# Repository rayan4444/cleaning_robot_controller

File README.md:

# Deck cleaning and staining robot

Hardware files for all the custom electronics in a deck cleaning and staining robot.
* Eagle files and documentation provided. See individual folder readme for details.
* Firmware for the STM32F407 was developed in C based on STM CubeMx libraries, but cannot be made public as of now.  

## Architecture

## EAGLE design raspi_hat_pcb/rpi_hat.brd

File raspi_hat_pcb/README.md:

# Raspberry Pi Hat

## Description
This board plugs onto a Raspberry pi and features:
- 1x ATSAMD21G18 MCU (Arduino Zero)
- 1x BNO055 IMU with jumpers to select the I2C host: Raspberry Pi or MCU
- 1x RS-485 transciever with jumper to select the UART host: Raspberry Pi or MCU
- 4x connectors for Ultrasonic sensors
- 1x FET driver for a small 5V fan to cool down the RPi

## Programming
The MCU on this board can normally be programmed directly via it's native USB port (using the microUSB connector on the board and in the Arduino IDE, choose Arduino Zero native USB as your Board. You might have to double-press the reset button before flashing). However the first time you use it, you need to burn the Arduino Zero bootloader on it first, using the SWD pins.

In this board, the SWD pins are connected to the Raspberry Pi connector so you can use the Raspberry pi to burn the bootloader, like explained in [this tutorial](https://learn.adafruit.com/programming-microcontrollers-using-openocd-on-raspberry-pi).

The soldered boards sent already have the Arduino bootloader burned and can be programmed directly.

## Hardware connections

MCU:

|ATSAMD21G18 Pin|Arduino Pin|Signal| Notes|
|:---:|:---:|:---:|:---:|
|PA5| A4 or 18|FAN_MCU| to toggle cooling fan from the MCU|
|PA10|1 or TX|MCU_TXD||
|PA11|0 or RX|MCU_RXD||
|PA12|22|RS485_DIR| controlling RS485 transceiver direction|
|PA15|5~|TRIG_B_| trigger pin for one pair of ultrasonic sensors|
|PA16| 11~|TRIG_|trigger pin for the other pair of ultrasonic sensors|
|PA17|13~|ECHO1| interrupt enabled|
|PA18|10~|ECHO2| interrupt enabled|
|PA19|12~|ECHO3|interrupt enabled|
|PA20|6~|ECHO4| interrupt enabled|
|PA21|7|IMU_INT| interrupt enabled|
|PA22|SDA|MCU_SDA| to IMU|
|PA23|SCL|MCU_SCL| to IMU|
|PA24|USB D-|USBD_N| to micro USB connector, for programming|
|PA25|USB D+|USBD_P| to micro USB connector, for programming|
|PA30|SWCLK|SWCLK|To Rpi,  for first time bootloader burning|
|PA31|SWDIO|SWDIO|To Rpi,  for first time bootlader burning|

Raspberry Pi:

|Raspberry Pi GPIO|Raspberry Pi Pin|Signal|Notes|
|:---:|:---:|:---:|:---:|
|GPIO 2|3|RPI_SDA|to IMU|
|GPIO 3|5|RPI_SCL|to IMU|
|GPIO 4|7|FAN_PI| to toggle cooling fan from the Rpi|
|GPIO 14|8|RPI_TX|RPI UART|
|GPIO 15|10|RPI_RX|RPI UART|
|GPIO 17|11|IMU_RST|to IMU|
|GPIO 18|12|RESET||
|GPIO 27|13|IMU_INT| to IMU|
|GPIO 24|18|MCU SWDIO|To burn bootloader to the MCU|
|GPIO 25|22|MCU SWCLK|To burn bootloader to the MCU|

Connectors:
- see pictures above

Jumper options:
- JP1 and JP2: select whether the MCU's UART talks to the Main board through RS485 or directly to the RPI
- JP3 and JP4: select whether the IMU connects to the MCU or the RPi

## Errata
Errors noticed when assemling:
- Pin 1 of IMU hard to spot
- Diode direction missing on D1
- R7 and C8 silkscreen unclear
- Ultrasonic sensors and RS485 connectors don't have a labelled pinout

Testing log:
- Tested all boards, bootloader burned.
- Communication with the IMU was tested with the Arduino MCU (I2C address 0x28): the jumpers were then set to commnuicate with the Raspberry Pi, but that communication hasn't been tested.
- Board 1: no problems
- Board 2: 5V red LED doesn't turn on but board works fine
- Board 3: no problems

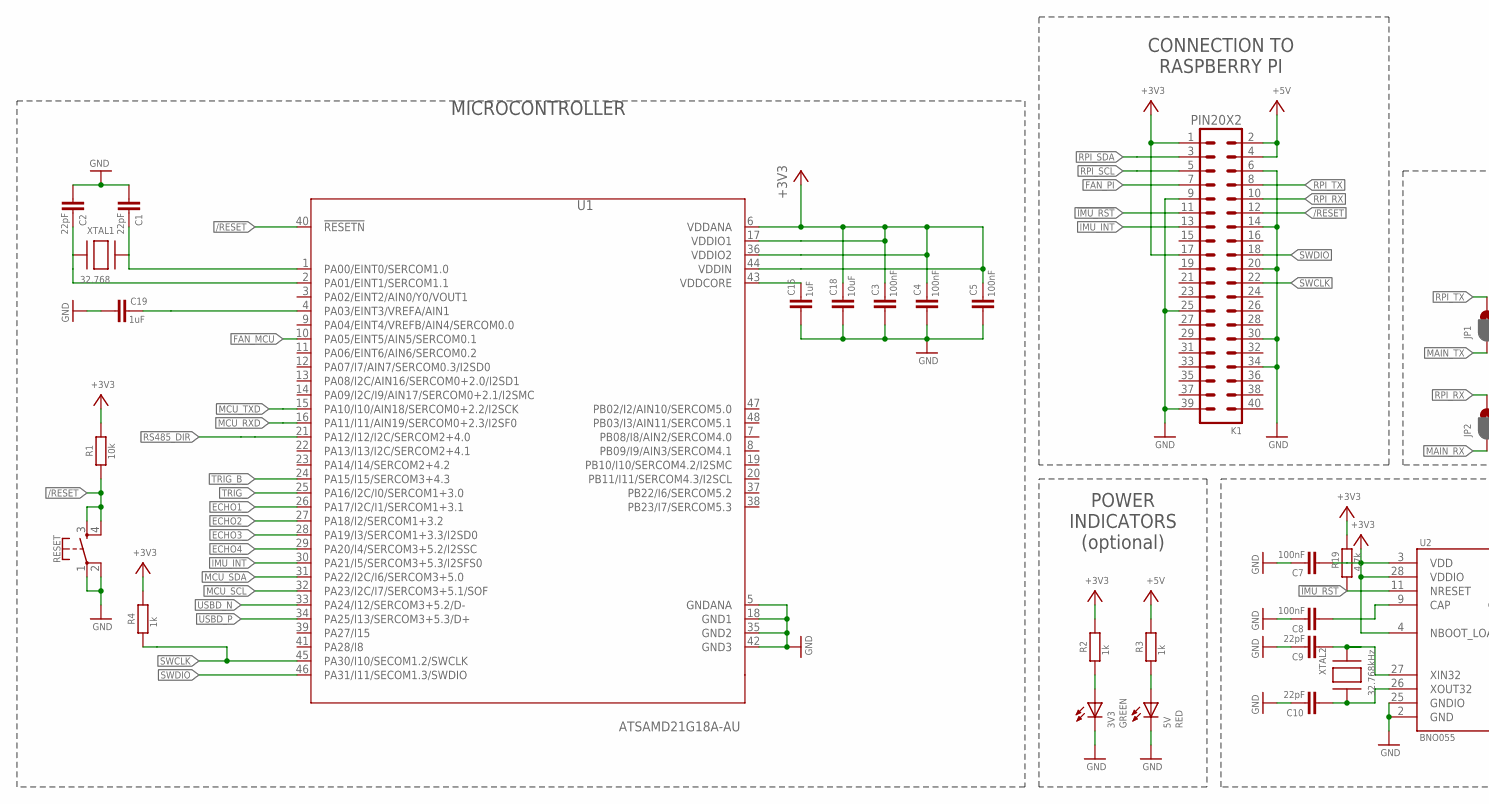
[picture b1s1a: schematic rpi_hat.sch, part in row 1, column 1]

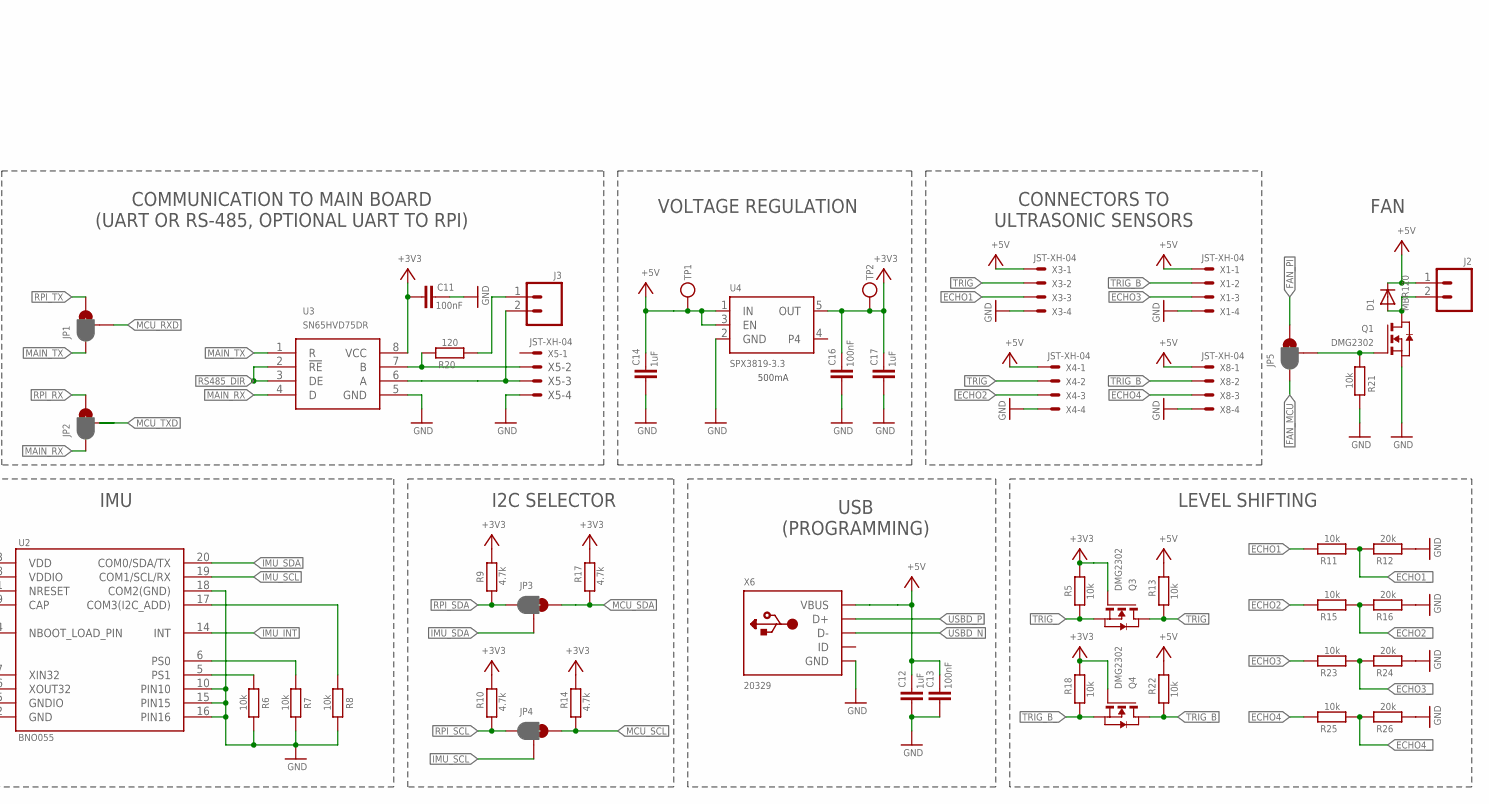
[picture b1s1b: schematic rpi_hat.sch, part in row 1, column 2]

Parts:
3V3: GREEN; CHIP-LED0603
5V: RED; CHIP-LED0603
C1, C2, C9, C10: 22pF; C0402
C3, C4, C5, C7, C8, C11, C13, C16: 100nF; C0402
C12, C14, C15, C17, C19: 1uF; C0402
C18: 10uF; C0402
D1: MBR120; SOD-123
J2, J3: CONN_02; 1X02
JP1, JP2, JP3, JP4, JP5: SPARKFUN-PASSIVES_JUMPER_PAD-3-1&2_NC_BY_PASTE; SPARKFUN-PASSIVES_PAD-HUMPER-3-1&2_NC_BY_PASTE_YES_SILK_FUL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
K1: PIN20X2; PIN_20X2
Q1, Q3, Q4: DMG2302; SOT-23
R1, R5, R6, R7, R8, R11, R13, R15, R18, R21, R22, R23, R25: 10k; R0402
R2, R3, R4: 1k; R0402
R9, R10, R14, R17, R19: 4.7k; R0402
R12, R16, R24, R26: 20k; R0402
R20: 120; R0402
RESET: MOMENTARY-SWITCH-SPST-2-SMD-4.6X2.8MM; TACTILE_SWITCH_SMD_4.6X2.8MM
TP1, TP2: MICROBUILDER_TESTPOINTROUND1MM; MICROBUILDER_TESTPOINT_ROUND_1MM
U1: ATSAMD21G18A-AU; QFP50P900X900X120-48N
U2: BNO055; LGA28R50P4X10_380X520X100
U3: SN65HVD75DR; SOIC127P600X175-8N
U4: SPX3819-3.3; SOT23-5
X1, X3, X4, X5, X8: JST-XH-04; JST-XH-04-PACKAGE-ROUND-PAD
X6: 20329; 4UCONN_20329_V2
XTAL1: 32.768; XTAL3215
XTAL2: 32.768kHz; ADAFRUIT2_XTAL3215

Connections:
!IMU_RST: K1.11, R19.1, U2.11 (NRESET)
+3V3: C3.1, C4.1, C5.1, C7.2, C11.2, C16.1, C17.1, C18.1, K1.1, K1.17, Q3.G, Q4.G, R1.2, R2.2, R4.2, R5.2, R9.2, R10.2, R14.2, R17.2, R18.2, R19.2, TP2.P$1, U1.6 (VDDANA), U1.17 (VDDIO1), U1.36 (VDDIO2), U1.44 (VDDIN), U2.3 (VDD), U2.4 (NBOOT_LOAD_PIN), U2.28 (VDDIO), U3.8 (VCC), U4.5 (OUT)
+5V: C12.1, C13.1, C14.1, D1.C, J2.1, K1.2, K1.4, R3.2, R13.2, R22.2, TP1.P$1, U4.1 (IN), U4.3 (EN), X1.1, X3.1, X4.1, X6.VBUS, X8.1
/RESET: K1.12, R1.1, RESET.3, RESET.4, U1.40 (!RESETN)
ECHO1: R11.2, X3.3
ECHO1_: R11.1, R12.2, U1.26 (PA17/I2C/I1/SERCOM1+3.1)
ECHO2: R15.2, X4.3
ECHO2_: R15.1, R16.2, U1.27 (PA18/I2/SERCOM1+3.2)
ECHO3: R23.2, X1.3
ECHO3_: R23.1, R24.2, U1.28 (PA19/I3/SERCOM1+3.3/I2SD0)
ECHO4: R25.2, X8.3
ECHO4_: R25.1, R26.2, U1.29 (PA20/I4/SERCOM3+5.2/I2SSC)
FAN_MCU: JP5.1, U1.10 (PA05/EINT5/AIN5/SERCOM0.1)
FAN_PI: JP5.3, K1.7
GND: 3V3.C, 5V.C, C1.2, C2.2, C3.2, C4.2, C5.2, C7.1, C8.1, C9.1, C10.1, C11.1, C12.2, C13.2, C14.2, C15.2, C16.2, C17.2, C18.2, C19.2, K1.6, K1.9, K1.14, K1.20, K1.25, K1.30, K1.34, K1.39, Q1.S, R6.2, R7.2, R8.2, R12.1, R16.1, R21.2, R24.1, R26.1, RESET.1, RESET.2, U1.5 (GNDANA), U1.18 (GND1), U1.35 (GND2), U1.42 (GND3), U2.2 (GND), U2.10 (PIN10), U2.15 (PIN15), U2.16 (PIN16), U2.18 (COM2(GND)), U2.25 (GNDIO), U3.5 (GND), U4.2 (GND), X1.4, X3.4, X4.4, X5.4, X6.BASE@1 (GND), X6.BASE@2 (GND), X6.GND, X6.SPRT@1 (GND), X6.SPRT@2 (GND), X6.SPRT@3 (GND), X6.SPRT@4 (GND), X8.4
IMU_INT: K1.13, U1.30 (PA21/I5/SERCOM3+5.3/I2SFS0), U2.14 (INT)
IMU_SCL: JP4.2, U2.19 (COM1/SCL/RX)
IMU_SDA: JP3.2, U2.20 (COM0/SDA/TX)
MAIN_RX: JP2.1, U3.4 (D)
MAIN_TX: JP1.1, U3.1 (R)
MCU_RXD: JP1.2, U1.16 (PA11/I11/AIN19/SERCOM0+2.3/I2SF0)
MCU_SCL: JP4.3, R14.1, U1.32 (PA23/I2C/I7/SERCOM3+5.1/SOF)
MCU_SDA: JP3.3, R17.1, U1.31 (PA22/I2C/I6/SERCOM3+5.0)
MCU_TXD: JP2.2, U1.15 (PA10/I10/AIN18/SERCOM0+2.2/I2SCK)
unnamed: J3.1, R20.1
unnamed: C2.1, U1.2 (PA01/EINT1/SERCOM1.1), XTAL1.P$1
unnamed: C1.1, U1.1 (PA00/EINT0/SERCOM1.0), XTAL1.P$2
unnamed: C15.1, U1.43 (VDDCORE)
unnamed: JP5.2, Q1.G, R21.1
unnamed: D1.A, J2.2, Q1.D
unnamed: R6.1, U2.5 (PS1)
unnamed: R7.1, U2.6 (PS0)
unnamed: C19.1, U1.4 (PA03/EINT3/VREFA/AIN1)
unnamed: C8.2, U2.9 (CAP)
unnamed: C10.2, U2.26 (XOUT32), XTAL2.P$1
unnamed: C9.2, U2.27 (XIN32), XTAL2.P$2
unnamed: 3V3.A, R2.1
unnamed: R8.1, U2.17 (COM3(I2C_ADD))
unnamed: 5V.A, R3.1
unnamed: R20.2, U3.7 (B), X5.2
unnamed: J3.2, U3.6 (A), X5.3
RPI_RX: JP2.3, K1.10
RPI_SCL: JP4.1, K1.5, R10.1
RPI_SDA: JP3.1, K1.3, R9.1
RPI_TX: JP1.3, K1.8
RS485_DIR: U1.21 (PA12/I12/I2C/SERCOM2+4.0), U3.2 (!RE), U3.3 (DE)
SWCLK: K1.22, R4.1, U1.45 (PA30/I10/SECOM1.2/SWCLK)
SWDIO: K1.18, U1.46 (PA31/I11/SECOM1.3/SWDIO)
TRIG: Q3.D, R13.1, X3.2, X4.2
TRIG_: Q3.S, R5.1, U1.25 (PA16/I2C/I0/SERCOM1+3.0)
TRIG_B: Q4.D, R22.1, X1.2, X8.2
TRIG_B_: Q4.S, R18.1, U1.24 (PA15/I15/SERCOM3+4.3)
USBD_N: U1.33 (PA24/I12/SERCOM3+5.2/D-), X6.D-
USBD_P: U1.34 (PA25/I13/SERCOM3+5.3/D+), X6.D+

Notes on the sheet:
CONNECTION TO RASPBERRY PI
IMU
CONNECTORS TO ULTRASONIC SENSORS
I2C SELECTOR
POWER INDICATORS (optional)
COMMUNICATION TO MAIN BOARD (UART OR RS-485, OPTIONAL UART TO RPI)
USB (PROGRAMMING)
VOLTAGE REGULATION
500mA
MICROCONTROLLER
LEVEL SHIFTING
FAN

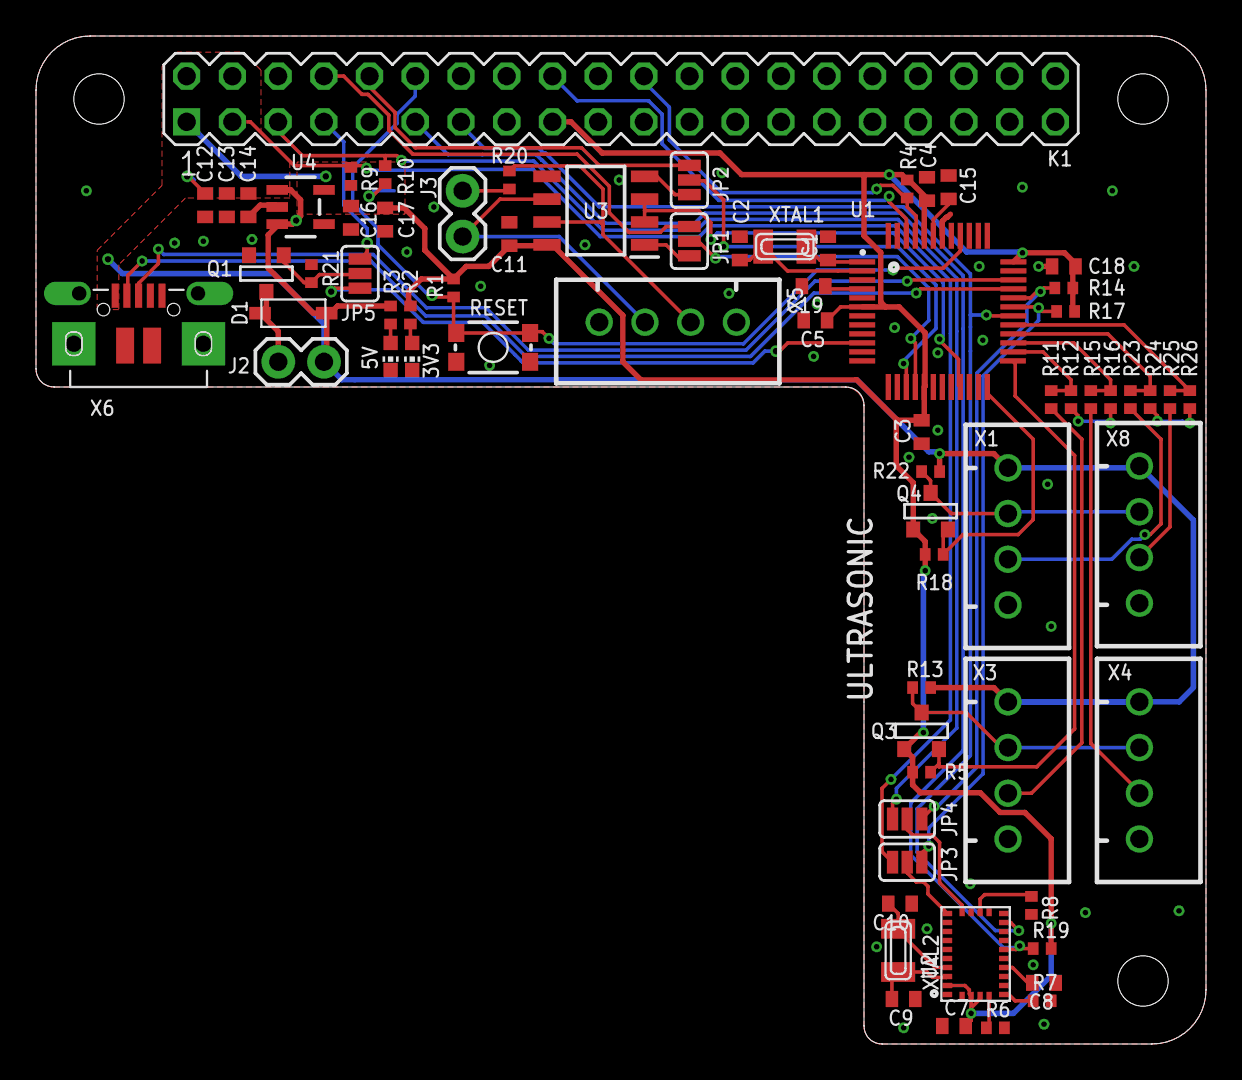
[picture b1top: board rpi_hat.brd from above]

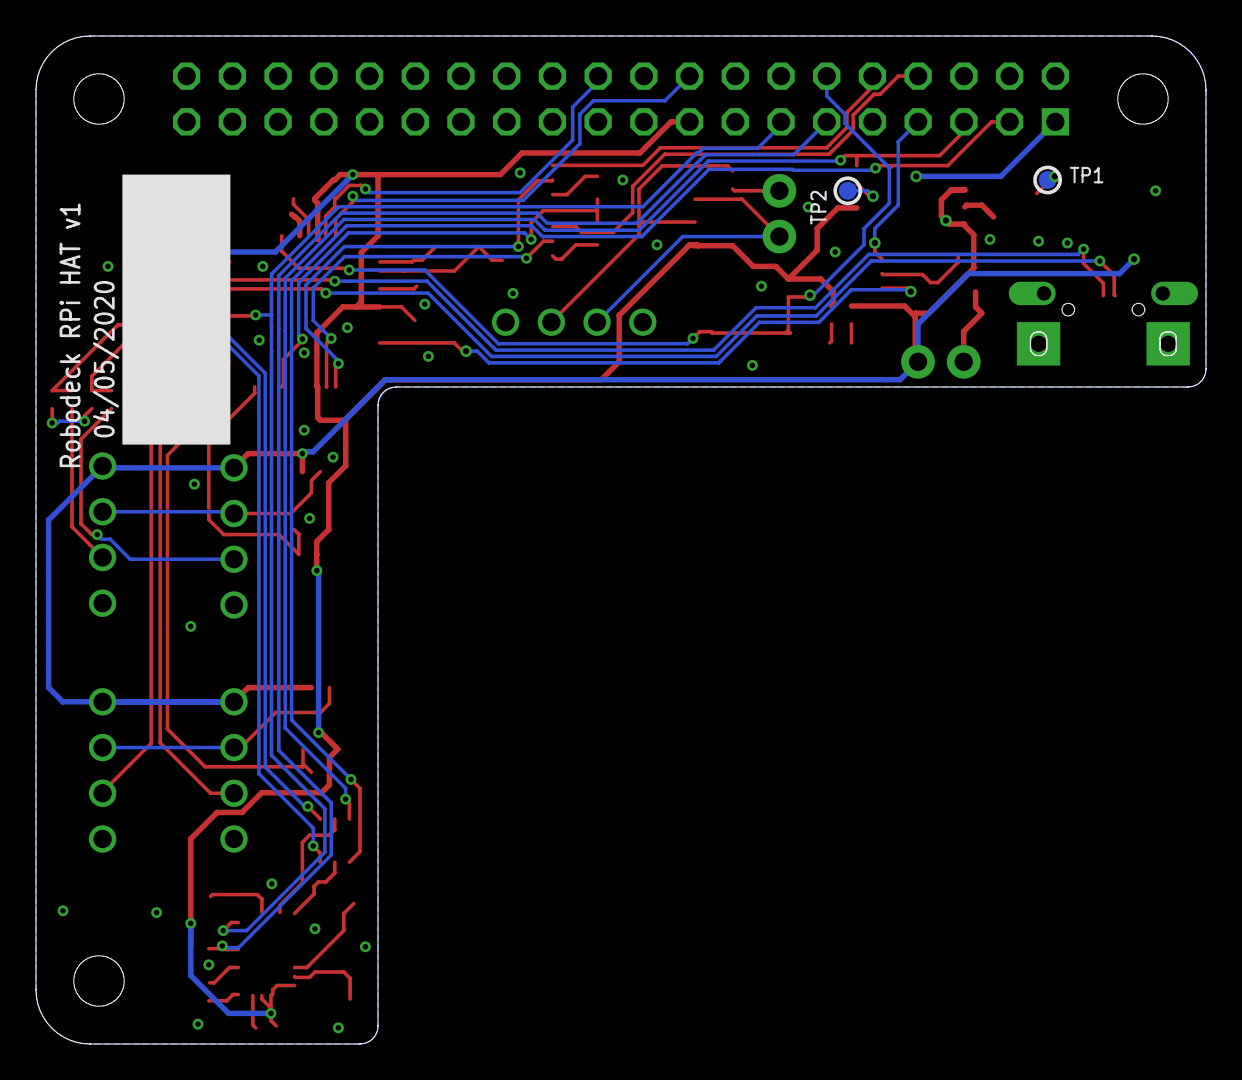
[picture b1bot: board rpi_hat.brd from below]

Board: 2 copper layers, 65.0 x 56.0 mm, 73 parts (2 on the bottom side), 54 nets.

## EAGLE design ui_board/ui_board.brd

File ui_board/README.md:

# UI board 

## Description
This board has the buttons and LED indicators for user interface:
* 3x momentary push buttons with some hardware debouncing
* 2x RGB LEDs, common anode.
* 1x Blue LED
* 1x Red LED tied to a green LED (tristate control)

## Hardware connections
On JST SH (1mm spacing) 8pin connector side, left to right:
|Pin|Signal| Notes|
|:---:|:---:|:---:|
|1|3V3|Supply to the board|
|2|Clean/Stain Button|LOW when pressed |
|3|Start/Stop Button|LOW when pressed|
|4|On/Off Button|LOW when pressed|
|5|I2C SCL|3.3V level, footprints for pullup resistors are available but not populated by default|
|6|I2C SDA|3.3V level, footprints for pullup resistors are available but not populated by default|
|7|GND||
|8|GND||

## Test sketch
There is an Arduino sketch to test the basic features of the UI board. A test cable with male Dupont ends is provided to help connect the UI board to a breadboard, Arduino or other development boards.

## Errata
Errors noted when assembling:
- MCP220008 pin one marking missing
- C4 and C5 silkscreen unclear
- LED cathode markings covered or too small
- LED1 and LED2 a little too close.

Test report:
- Board 1: nothing wrong so far
- Board 2: nothing wrong so far
- Board 3: nothing wrong so far

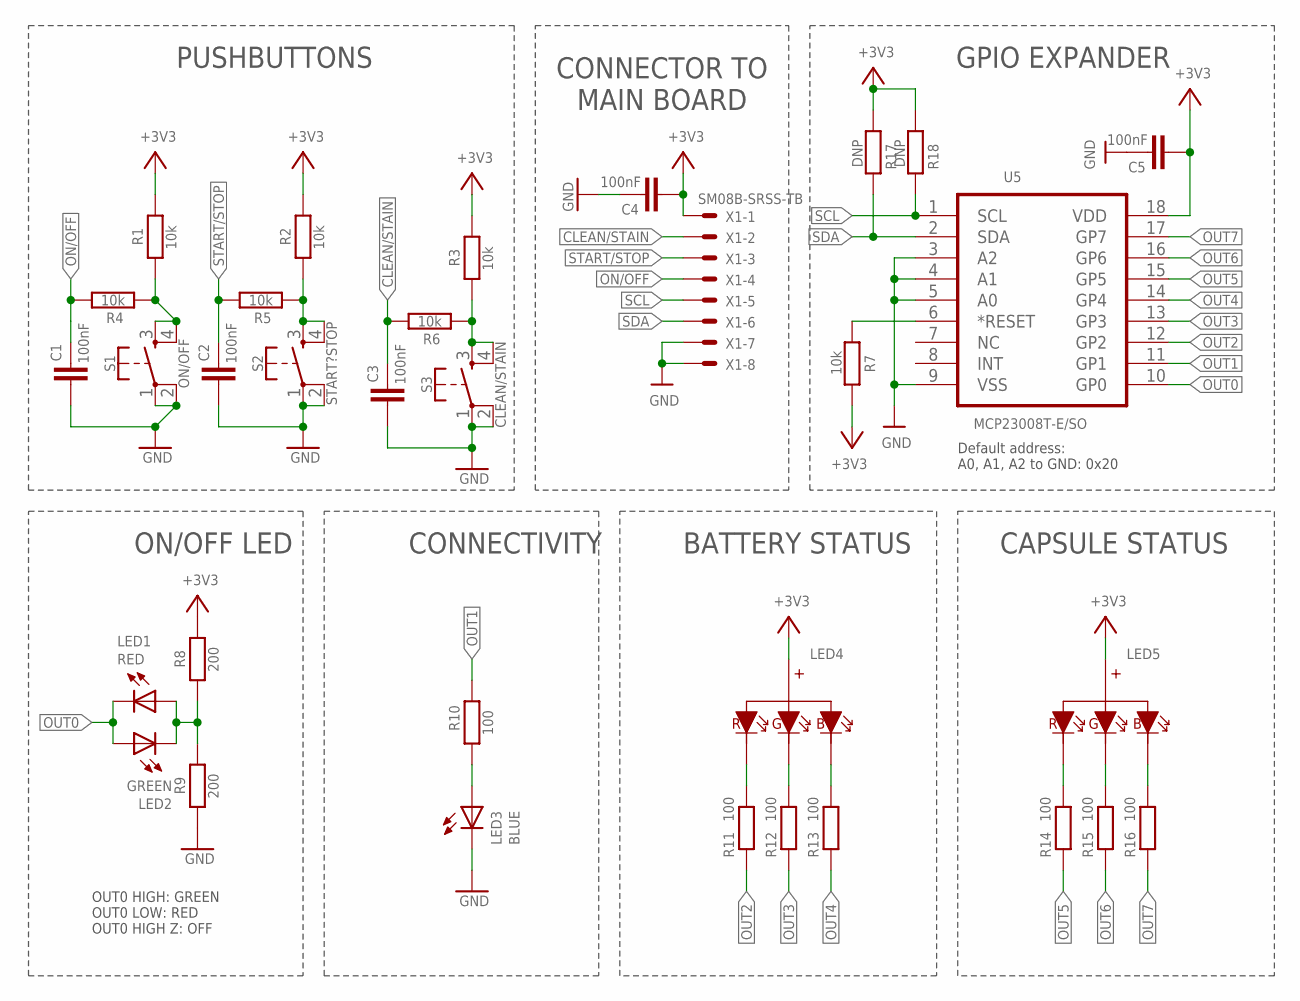
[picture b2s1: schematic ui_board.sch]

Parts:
C1, C2, C3, C4, C5: 100nF; C0402
LED1: RED; CHIP-LED0603
LED2: GREEN; CHIP-LED0603
LED3: BLUE; CHIP-LED0603
LED4, LED5: RGB_CAV1; 19-037A/RSGHBHW
R1, R2, R3, R4, R5, R6, R7: 10k; R0402
R8, R9: 200; R0402
R10, R11, R12, R13, R14, R15, R16: 100; R0402
R17, R18: DNP; R0402
S1: ON/OFF; TACTILE_SWITCH_SMD_5.2MM
S2: START?STOP; TACTILE_SWITCH_SMD_5.2MM
S3: CLEAN/STAIN; TACTILE_SWITCH_SMD_5.2MM
U5: MCP23008T-E/SO; SOIC127P1030X265-18N
X1: SM08B-SRSS-TB

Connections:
+3V3: C4.2, C5.2, LED4.A, LED5.A, R1.2, R2.2, R3.2, R7.2, R8.2, R17.1, R18.1, U5.18 (VDD), X1.1
CLEAN/STAIN: C3.1, R6.2, X1.2
GND: C1.2, C2.2, C3.2, C4.1, C5.1, LED3.C, R9.1, S1.1, S1.2, S2.1, S2.2, S3.1, S3.2, U5.3 (A2), U5.4 (A1), U5.5 (A0), U5.9 (VSS), X1.7, X1.8
unnamed: LED3.A, R10.1
unnamed: LED4.R, R11.2
unnamed: R1.1, R4.1, S1.3, S1.4
unnamed: R2.1, R5.1, S2.3, S2.4
unnamed: R3.1, R6.1, S3.3, S3.4
unnamed: LED4.G, R12.2
unnamed: LED4.B, R13.2
unnamed: LED5.R, R14.2
unnamed: LED5.G, R15.2
unnamed: LED5.B, R16.2
unnamed: LED1.A, LED2.C, R8.1, R9.2
unnamed: R7.1, U5.6 (*RESET)
ON/OFF: C1.1, R4.2, X1.4
OUT0: LED1.C, LED2.A, U5.10 (GP0)
OUT1: R10.2, U5.11 (GP1)
OUT2: R11.1, U5.12 (GP2)
OUT3: R12.1, U5.13 (GP3)
OUT4: R13.1, U5.14 (GP4)
OUT5: R14.1, U5.15 (GP5)
OUT6: R15.1, U5.16 (GP6)
OUT7: R16.1, U5.17 (GP7)
SCL: R18.2, U5.1 (SCL), X1.5
SDA: R17.2, U5.2 (SDA), X1.6
START/STOP: C2.1, R5.2, X1.3

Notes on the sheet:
ON/OFF LED
CONNECTIVITY
BATTERY STATUS
CAPSULE STATUS
PUSHBUTTONS
CONNECTOR TO MAIN BOARD
Default address: A0, A1, A2 to GND: 0x20
OUT0 HIGH: GREEN OUT0 LOW: RED OUT0 HIGH Z: OFF
GPIO EXPANDER

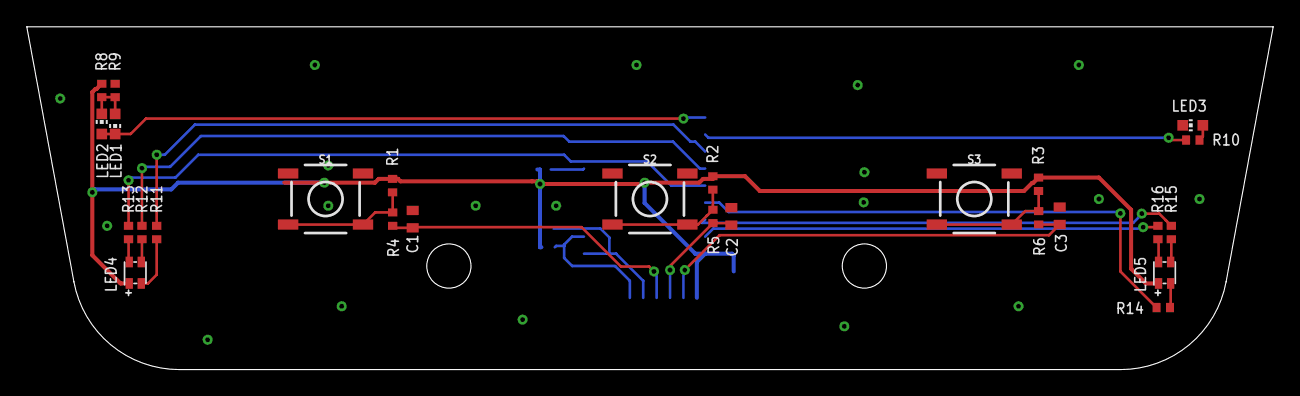
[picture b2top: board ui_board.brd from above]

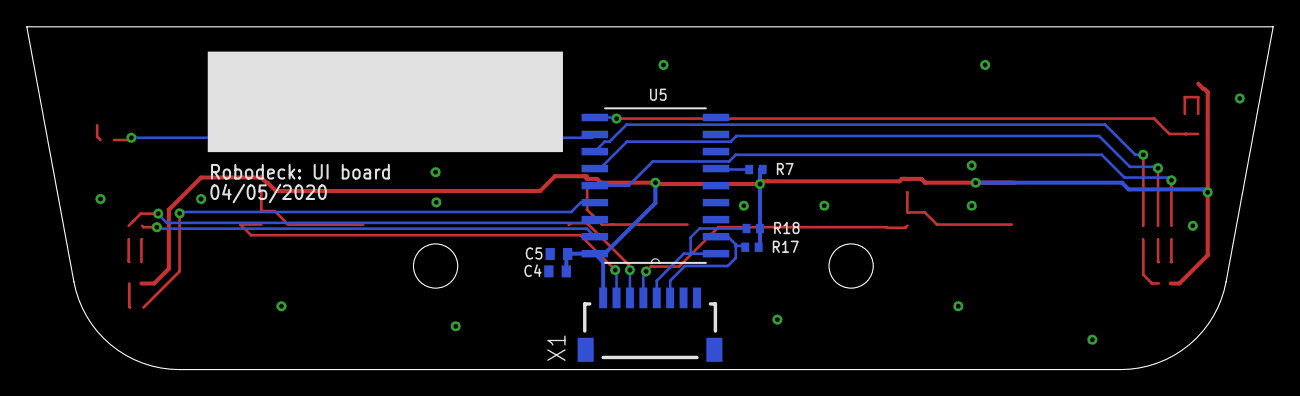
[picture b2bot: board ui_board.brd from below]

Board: 2 copper layers, 93.0 x 25.6 mm, 33 parts (7 on the bottom side), 27 nets.

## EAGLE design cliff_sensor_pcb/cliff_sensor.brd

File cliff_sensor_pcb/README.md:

# Robodeck Cliff sensor 

## Description
This small board features a single TCRT5000 sensor and a votlage controlled current source to control the brightness of the IR LED in the sensor if needed/wanted. 

## Hardware connections 
JST XH Connector 4Pin, top view (left on the picture above), left to right:
- GND
- CLIFF_OUT: analog output of the cliff sensor
- CLIFF_CTRL: input to the voltage controlled current source
- 3V3

In constant current mode: 
- Solder a resistor on R1 to set the current 
- Solder JP1 to GND

In controlled current mode: 
- Connect CLIFF_CTRL signal to an analog voltage source (ex: STM32 DAC)
- Solder a 0 ohm resistor to R1
- Solder JP1 to CTRL

## Errata
Errors noted when assembling: 
- forgot to label pin signals at the back 

Testing log:
- Not tested yet

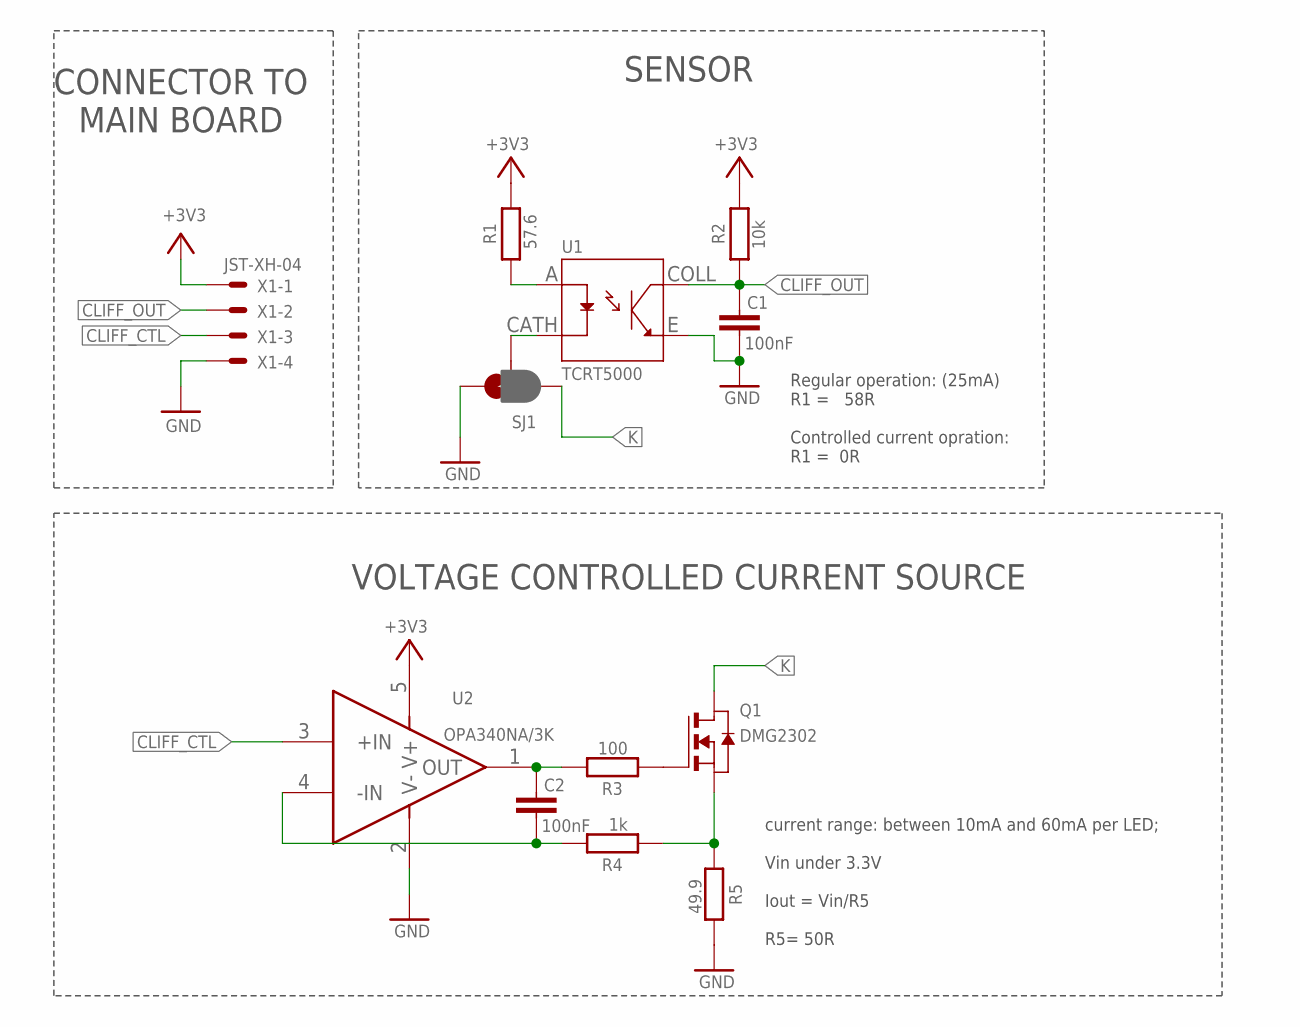
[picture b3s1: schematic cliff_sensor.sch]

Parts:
C1, C2: 100nF; C0402
Q1: DMG2302; SOT-23
R1: 57.6; R0402
R2: 10k; R0402
R3: 100; R0402
R4: 1k; R0402
R5: 49.9; R0402
SJ1: SPARKFUN-PASSIVES_JUMPER_PAD-3-1&2_NC_BY_PASTE; SPARKFUN-PASSIVES_PAD-HUMPER-3-1&2_NC_BY_PASTE_YES_SILK_FUL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
U1: TCRT5000; OPTO_TCRT5000
U2: OPA340NA/3K; SOT95P280X145-5N
X1: JST-XH-04; JST-XH-04-PACKAGE-ROUND-PAD

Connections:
+3V3: R1.2, R2.2, U2.5 (V+), X1.1
CLIFF_CTL: U2.3 (+IN), X1.3
CLIFF_OUT: C1.2, R2.1, U1.COLL, X1.2
GND: C1.1, R5.2, SJ1.3, U1.E, U2.2 (V-), X1.4
K: Q1.D, SJ1.1
unnamed: SJ1.2, U1.CATH
unnamed: C2.2, R3.2, U2.1 (OUT)
unnamed: C2.1, R4.2, U2.4 (-IN)
unnamed: Q1.G, R3.1
unnamed: Q1.S, R4.1, R5.1
S_IN2: R1.1, U1.A

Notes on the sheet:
Regular operation: (25mA) R1 = 58R Controlled current opration: R1 = 0R
SENSOR
VOLTAGE CONTROLLED CURRENT SOURCE
current range: between 10mA and 60mA per LED; Vin under 3.3V Iout = Vin/R5 R5= 50R
CONNECTOR TO MAIN BOARD

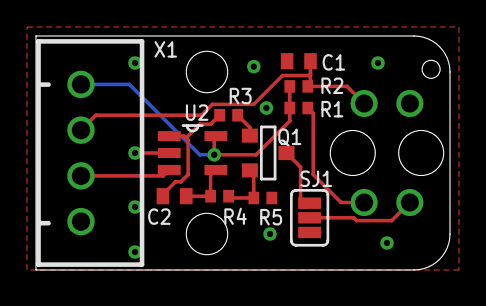
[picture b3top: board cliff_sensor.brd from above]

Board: 2 copper layers, 23.0 x 13.0 mm, 12 parts (1 on the bottom side), 11 nets.

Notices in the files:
parts and their libraries:
microbuilder: This work is placed in the public domain, and may be freely used for commercial and non-commercial work with the following conditions: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
SparkFun-Switches: Licensing: Creative Commons ShareAlike 4.0 International - https://creativecommons.org/licenses/by-sa/4.0
